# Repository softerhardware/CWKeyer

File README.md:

# CW Keyer for the Hermes-Lite and other SDR software

This project is a CW keyer for amateur radio. The hardware connects to a PC with USB. It then appears as an audio device for radio sound output and microphone input. It is also a Midi device to signal key up/down to the PC software, and a serial device for a connection to logging or other software on the PC. It is designed for the [Hermes-Lite 2.0](http://www.hermeslite.com/) or other SDR software. The radio sound is sent to the keyer and the keyer generates a sidetone, mixes it with the audio and sends it to the headphones or speaker. The sidetone has zero delay and is suitable for high speed CW. The keyer can also be used with a regular analog radio by using the key and PTT outputs. This project is currently a DIY project with instructions below for those who feel comfortable with some light soldering and Arduino programming.

## Hardware

The hardware consists of a carrier board as shown below and a [Teensy 4](https://www.pjrc.com/teensy/) microcontroller.
The Teensy can be purchased from [Teensy](https://www.pjrc.com/store/teensy40.html) or from [sparkfun](https://www.sparkfun.com/), [adafruit](https://www.adafruit.com/), [mouser](https://www.mouser.com/), [digikey](https://www.digikey.com/) or [amazon](https://www.amazon.com/). Make sure to order the Teensy 4.

## Software

Keyer software must be loaded into the Teensy 4 microcontroller. The Teensy 4 is programmed via a usb connection to a host computer. First, download and install the Teensy loader application for your operating system as described on [this page](https://www.pjrc.com/teensy/loader.html). Then start the teensy application. Press the programming button on the Teensy and the teensy app will change to show a picture of the board. Then select the ".hex" program file, select "program" and then "reboot".

There are currently two keyer programs available, the "hasak" and the "TeensyWinkeyEmulator". Click on the "firmware" link above, and click through the directories until you find the hex file you want. The file will appear as a table of numbers with a "Raw" button on the upper right side. Right click the Raw button and select "Save link as". Make sure the file name ends in ".hex". Save the hex file and use it to program the Teensy.

## Ctrlr

TBD: Basic description, download and use instructions for Ctrlr MIDI control panel.

## Software Development

To write your own keyer software or to contribute to software development first clone this repository.
This git repository uses several submodules to collect various projects into a single repository. You must initialize submodules when intially cloning:

git clone --recurse-submodules git@github.com:softerhardware/CWKeyer.git

After that, also be sure to pull updates from submodules:

git pull --recurse-submodules

You can find more details about how to work with git submodules on the internet.

### Teensy Libraries

Current development is done using [Arduino IDE 1.8.19](https://www.arduino.cc/en/software) and [Teensyduino 1.56](https://www.pjrc.com/teensy/td_download.html). Please make sure those are installed.

Updated libraries are required for glitchless 48kHz audio with the CW keyer hardware. These libraries are provided in this git repository. An easy way to use these libraries is to add symbolic links to the new libraries from the arduino IDE install. This is described below for Linux and MacOS systems.

Be sure to select the "Teensy 4.0" board in the Tools-->Boards-->Teensiduino menu, and to select the "Serial + Midi + Audio" USB model in the Tools-->USB type menu,
otherwise compilation will fail.

Install teensy  library update for linux:
-----------------------------------------

 1. cd arduino-1.8.19/hardware/teensy/avr
 2. rm -rf cores   (This must be removed or moved outside of the arduino-1.8.19 area otherwise arduino will still pickup this code)
 3. ln -s /home/shaynal/CWKeyer/libraries/teensy/cores .   (Substitute the path for your local git pull of the CWKeyer repository)
 4. cd libraries
 5. rm -rf Audio   (See step 2 comments)
 6. ln -s /home/shaynal/CWKeyer/libraries/teensy/Audio .   (See step 3 comments)
 7. ln -s /home/shaynal/CWKeyer/libraries/teensy/CWKeyerShield .   (See step 3 comments)

Install teensy library update for MacOS:
----------------------------------------

(Added by DL1YCF. Note this is best done from the "terminal" app, then this is very similar to the
linux case).

All the libraries are inside the Teensyduino "app" file bundle (which is a directory tree)
/Applications/Teensyduino.app. Locate a sub-folder called "Audio", this will point you to
the libraries for the Teensy. Normally this is located in

/Applications/Teensyduino.app/Contents/Java/hardware/teensy/avr/libraries

You can copy the "Audio" folder within that folder to a safe place (or just delete it),
and do the same to the "cores" folder one step higher, that is, the "cores" folder within

/Applications/Teensyduino.app/Contents/Java/hardware/teensy/avr

Then proceed as in the linux case, that is, add a symbolic link named "cores" in the .../teensy/avr
folder and two symbolic links called "Audio" and "CWKeyerShield" in the
.../teensy/avr/libraries folder, that point to the directories "Audio", "cores" and
"CWKeyerShield" where you have placed them after down-loading from this repository.

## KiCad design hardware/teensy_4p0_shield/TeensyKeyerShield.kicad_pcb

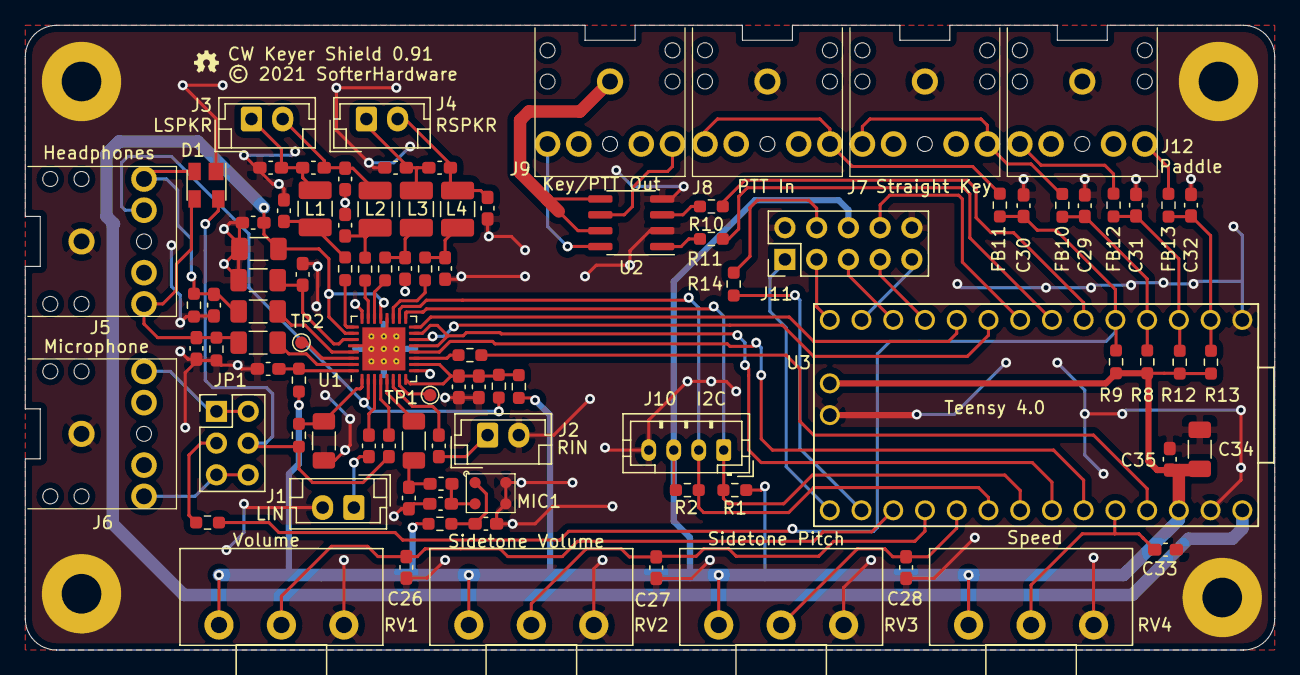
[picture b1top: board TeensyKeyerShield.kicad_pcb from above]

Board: 2 copper layers, 100.0 x 50.0 mm, 98 parts (0 on the bottom side), 74 nets.

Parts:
C1, C6, C7, C8, C12, C22, C34: 47uF; C_1206_3216Metric_Pad1.33x1.80mm_HandSolder
C2, C3, C4, C5, C10, C25, C26, C27, C28, C33, C35: 0.1uF; C_0603_1608Metric_Pad1.08x0.95mm_HandSolder
C9, C11, C15: 1uF; C_0603_1608Metric_Pad1.08x0.95mm_HandSolder
C13, C14, C18, C19, C20, C21, C23, C24, C36, C37, C38, C39: 33pF; C_0603_1608Metric_Pad1.08x0.95mm_HandSolder
C16, C17: 470nF; C_0603_1608Metric_Pad1.08x0.95mm_HandSolder
C29, C30, C31, C32: 10nF; C_0603_1608Metric_Pad1.08x0.95mm_HandSolder
D1: SP0503BAHTG; SOT-143
FB1, FB2, FB3, FB4, FB5, FB6, FB7, FB8, FB10, FB11, FB12, FB13: Ferrite_Bead_Small; R_0603_1608Metric_Pad0.98x0.95mm_HandSolder
J1, J2, J3, J4: Conn_01x02; JST_EH_B2B-EH-A_1x02_P2.50mm_Vertical
J5, J6, J7, J8, J9, J12: AudioJack3_SwitchTR; STEREO_TRS
J10: Conn_01x04; JST_PH_B4B-PH-K_1x04_P2.00mm_Vertical
J11: Conn_02x05_Odd_Even; PinHeader_2x05_P2.54mm_Vertical
JP1: Conn_02x03_Odd_Even; PinHeader_2x03_P2.54mm_Vertical
L1, L2, L3, L4: 15uH; L_1210_3225Metric_Pad1.42x2.65mm_HandSolder
L5: BLM18BD252SN1; L_0603_1608Metric_Pad1.05x0.95mm_HandSolder
MH1, MH2, MH3, MH4: TestPoint_Alt; MH
MIC1: MEMSMIC
R1, R2: 4.7K; R_0603_1608Metric_Pad0.98x0.95mm_HandSolder
R3, R6, R7: 47K; R_0603_1608Metric_Pad0.98x0.95mm_HandSolder
R4: 33; R_0603_1608Metric_Pad0.98x0.95mm_HandSolder
R5: 680; R_0603_1608Metric_Pad0.98x0.95mm_HandSolder
R8, R9, R12, R13: DNI; R_0603_1608Metric_Pad0.98x0.95mm_HandSolder
R10, R11, R14: 470; R_0603_1608Metric_Pad0.98x0.95mm_HandSolder
RV1, RV2, RV3, RV4: 25K; Potentiometer_Piher_T-16H_Single_Horizontal
TP1, TP2: TestPoint; TestPoint_Pad_D1.0mm
U1: WM8960; QFN-32-1EP_5x5mm_P0.5mm_EP3.45x3.45mm_ThermalVias
U2: MOCD217R2M; SOIC-8_3.9x4.9mm_P1.27mm
U3: Teensy4.0; Teensy40

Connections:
+3V3: C34.1, C35.1, FB1.2, FB2.2, FB8.1, J10.3, J11.6, R1.1, R2.1, R8.2, R9.2, R12.2, R13.2, RV1.1, RV2.1, RV3.1, RV4.1, U3.16, U3.31
+5V: C1.1, C5.1, U1.21, U1.26, U3.33
ADCDAT: U1.16, U3.10
BCLK: U1.12, U3.28
DACDAT: U1.14, U3.9
GND: C1.2, C2.2, C3.1, C4.2, C5.2, C6.1, C10.2, C12.2, C13.2, C14.2, C18.1, C19.1, C20.1, C21.1, C23.2, C24.2, C25.2, C26.2, C27.2, C28.2, C29.2, C30.2, C31.2, C32.2, C33.2, C34.2, C35.2, C36.1, C37.1, C38.1, C39.1, D1.1, J1.2, J2.2, J5.S, J6.S, J7.S, J8.S, J10.4, J11.2, J11.10, J12.S, MH1.1, MH2.1, MH3.1, MH4.1, MIC1.2, MIC1.3, R6.1, R7.1, RV1.3, RV2.3, RV3.3, RV4.3, U1.9, U1.20, U1.24, U1.28, U1.33, U2.2, U2.4, U3.1, U3.17, U3.32
JACKDET: J5.RN, R3.1, U1.2
LRCLK: U1.13, U1.15, U3.27
MCLK: R4.2, U3.30
MEMSMIC: C22.2, U1.5
MICPTT: C30.1, FB7.2, FB11.1, R9.1, U3.5
unnamed: C2.1, C3.2, FB1.1, R3.2, U1.8, U1.10
unnamed: C4.1, FB2.1, U1.32
unnamed: C6.2, R5.2, U1.1
unnamed: C7.2, U1.29
unnamed: C8.2, U1.31
unnamed: C9.1, U1.3
unnamed: C9.2, J1.1
unnamed: C10.1, C12.1, U1.27
unnamed: C11.1, U1.6
unnamed: C11.2, J2.1
unnamed: C7.1, C13.1, D1.2, J5.R, R6.2
unnamed: C8.1, C14.1, D1.3, J5.T, R7.2
unnamed: C15.1, D1.4, JP1.4, R5.1
unnamed: C15.2, U1.4
unnamed: C16.1, C18.2, J3.1, L1.2
unnamed: C16.2, C19.2, J3.2, L2.2
unnamed: C17.1, C20.2, J4.1, L3.2
unnamed: C17.2, C21.2, J4.2, L4.2
unnamed: C22.1, C23.1, L5.1
unnamed: C24.1, L5.2, MIC1.4
unnamed: C25.1, FB8.2, MIC1.1
unnamed: C26.1, RV1.2, U3.22
unnamed: C27.1, RV2.2, U3.23
unnamed: C28.1, RV3.2, U3.24
unnamed: C29.1, FB10.1, R8.1, U3.4
unnamed: C31.1, FB12.1, R12.1, U3.3
unnamed: C32.1, FB13.1, R13.1, U3.2
unnamed: C33.1, RV4.2, U3.29
unnamed: C36.2, FB3.1, L1.1
unnamed: C37.2, FB4.1, L2.1
unnamed: C38.2, FB5.1, L3.1
unnamed: C39.2, FB6.1, L4.1
unnamed: FB3.2, U1.25
unnamed: FB4.2, U1.23
unnamed: FB5.2, U1.22
unnamed: FB6.2, U1.19
unnamed: FB7.1, JP1.3
unnamed: FB10.2, J7.R, J7.T
unnamed: FB11.2, J8.R, J8.T
unnamed: FB12.2, J12.T
unnamed: FB13.2, J12.R
unnamed: J6.R, JP1.1, JP1.2
unnamed: J6.T, JP1.5, JP1.6
unnamed: J9.R, U2.6
unnamed: J9.S, U2.5, U2.7
unnamed: J9.T, U2.8
unnamed: J11.1, U3.20
unnamed: J11.3, U3.14
unnamed: J11.4, R14.2
unnamed: J11.5, U3.12
unnamed: J11.7, U3.11
unnamed: J11.8, U3.8
unnamed: J11.9, U3.13
unnamed: R4.1, U1.11
unnamed: R10.1, U3.6
unnamed: R10.2, U2.3
unnamed: R11.1, U3.7
unnamed: R11.2, U2.1
unnamed: R14.1, U3.21
unnamed: TP1.1, U1.7
unnamed: TP2.1, U1.30
SCLK: J10.1, R1.2, U1.17, U3.26
SDIN: J10.2, R2.2, U1.18, U3.25

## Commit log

2021-10-26 TeensyKeyerShield floorplanning
2021-10-29 Updated with some routing
2021-11-01 Most routing done
2021-11-04 Mostly done with routing and silkscreen
2021-11-06 Added ibom.html
2021-11-08 Renaming
2021-11-08 Release 0p9
2021-11-08 Add frontpanel
2021-11-10 0p91 shield release
2021-12-05 Updated submodules
2021-12-14 Updated keyer and audio library
2021-12-24 Refined support for pots
2022-01-03 New commits to TeensyWinkeyEmulator and k3ng_cw_keyer submodules
2022-01-09 Updates to TeensyWinkeyEmulator and Audio
2022-01-09 Removed k3ng_cw_keyer
2022-01-09 Updated Audio and cores
2022-01-10 Change path to TeensyWinkeyEmulator
2022-01-10 Moved sgtl5000 .hex files into own release subdirectory
2022-01-10 Updated readme and TeensyWinkeyEmulator .hex file
2022-01-14 Updates to hasak and TeensyWinkeyEmulator, added cwkeyer.py
2022-01-20 Pointed back to dl1ycf submodule
2022-01-23 Added CWKeyerShield to library
2022-01-24 Update README.md
    Added MacOS instructions.
2022-01-25 Update README.md
    Updated instructions (Boards and USB type menu).
2022-01-31 Pulled TeensyWinkeyEmulator updates
2022-01-31 Pulled rework of wm8960 API
2022-01-31 Added wm8960 commands to CWKeyerShiled and cwkeyer.py
2022-01-31 Unified midi response in CWKeyerShield
2022-01-31 a) Improved handling of Pots. Speed pot now has larger "delta v/delta phi" for large speeds. b) PTT and CW-key handling now in "Shield" module c) Initialized microphone input d) handling of PTT now f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
2022-02-01 Converted the software to using a single MIDI channel
2022-02-01 removed an #ifdef associated with obsolete "potentiometer treatment"
2022-02-03 Pulled in TeensyWinkeyEmulator updates
2022-02-03 Pulled Keyer update
2022-02-03 Updating to current hasak origin main.
2022-02-07 New commit
2022-02-08 advances to latest commit of TeensyWinkeyEmulator
2022-02-09 updated to latest hasak commit
2022-02-10 Make side tone and master volume changes "smoother"
2022-02-10 pulled latest version
2022-02-10 Updating to hot out of the box configuration.
2022-02-10 Fixed broken noteEnable mask.
2022-02-10 Corrected note logic.
2022-02-11 a) avoid "reserved" MIDI controllers, b) allow key-down and PTT by incoming MIDI messages
2022-02-11 typo in comment
2022-02-12 Added nrpn support, more meaningful midi cc assignments
2022-02-12 Changes to implement NRPNs.
2022-02-12 Updated hasak release.
2022-02-12 Redid the merge to retain more of Steve's code with minimal changes.
2022-02-12 Cleaned up compile time errors and tested on TeensyWinkeyEmulator.
2022-02-12 Added hasak.json to the release.
2022-02-12 Updated release of the day, added hasak.json.
2022-02-13 Pulled new firmware versions
2022-02-13 Add side tone onto RX audio instead of replacing it.
2022-02-13 Avoid "overdrive" when blending RX and side tone
2022-02-13 New hex file for TeensyWinkeyEmulator
2022-02-13 New pull
2022-02-14 Constructor defaults, On/Off at 64/63, MIDI keydown/ptt accepted as notes
2022-02-14 Removed MIDI channel/note assignment from constructure, added interface to set these.
2022-02-14 latest pull
2022-02-14 latest pull of the TeensyWinkeyEmulator
2022-02-14 Reverse change to constructor
2022-02-14 small correction to the "smooth audio blending" update
2022-02-14 updated TeensyWinkeyEmulator submodule
2022-02-15 Added accessor functions for volatile values
2022-02-15 pulled latest TeensyWinkeyEmulator commits
2022-02-15 New TeensyWinkeyEmulator hex file.
2022-02-16 Make "soft audio blending" compatible with the mute option
2022-02-16 pulles latest commit for TeensyWinkeyEmulator
2022-02-16 Created "own" directory for TeensyWinkeyEmulator Release Hex File.
2022-02-17 New hex file
2022-02-17 New pull on TeensyWinKeyEmulator
2022-02-21 Modified README.md to provide a more elementary explanation for new users.
2022-02-21 I modified README.md because the hex file download links did not work.
2022-02-22 Upon setup, pull CW and PTT output lines LOW.
2022-02-23 Two hex files for two different hardware setups, and a Readme for that.
2022-02-23 new commits for TeensyWinkeyEmulator
2022-02-28 Updated TeensyWinkeyEmulator (should be close to final now)
2022-02-28 pull of fix
2023-10-20 Mic Bias on by default for wm8960
2024-03-20 Increase resilience through pointer checking
2024-03-20 tracked new commits to external packages (Audio, Cores, Emulator)
2025-03-25 Added a comment on the "input level" for the microphone jack
2025-03-25 Some further notes on the mic input added

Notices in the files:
hardware/teensy_4p0_shield/TeensyKeyerShield.kicad_pcb:
© 2021 SofterHardware
